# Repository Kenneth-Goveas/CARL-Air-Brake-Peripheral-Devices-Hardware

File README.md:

# CARL Air Brake Peripheral Devices Hardware

This repository contains the electronic hardware design for the peripheral
devices module of the [CARL Air Brake][cab-repo] computer. The CARL Air Brake
computer automatically controls a rocket air brake in flight, so that the
vehicle attains an apogee at the desired altitude. Its peripheral devices module
contains the necessary sensors and the brake actuator.

![Top view of the peripheral devices module](
  ./documentation/images/top_view.png
)

![Bottom view of the peripheral devices module](
  ./documentation/images/bottom_view.png
)

Detailed documentation for this repository can be found in the following files.

- [description.md][des]:
  Detailed description of the peripheral devices module.
- [cloning.md][cln]:
  Properly cloning this repository along with all its submodules.
- [prerequisites.md][req]:
  Necessary software for viewing and editing the electronic design.
- [organization.md][org]:
  Directory structure and organization of files in this repository.
- [flashing.md][fsh]:
  Flashing software onto the peripheral devices module.

[des]:      ./documentation/description.md
[cln]:      ./documentation/cloning.md
[req]:      ./documentation/prerequisites.md
[org]:      ./documentation/organization.md
[fsh]:      ./documentation/flashing.md

[cab-repo]: https://github.com/Kenneth-Goveas/CARL-Air-Brake

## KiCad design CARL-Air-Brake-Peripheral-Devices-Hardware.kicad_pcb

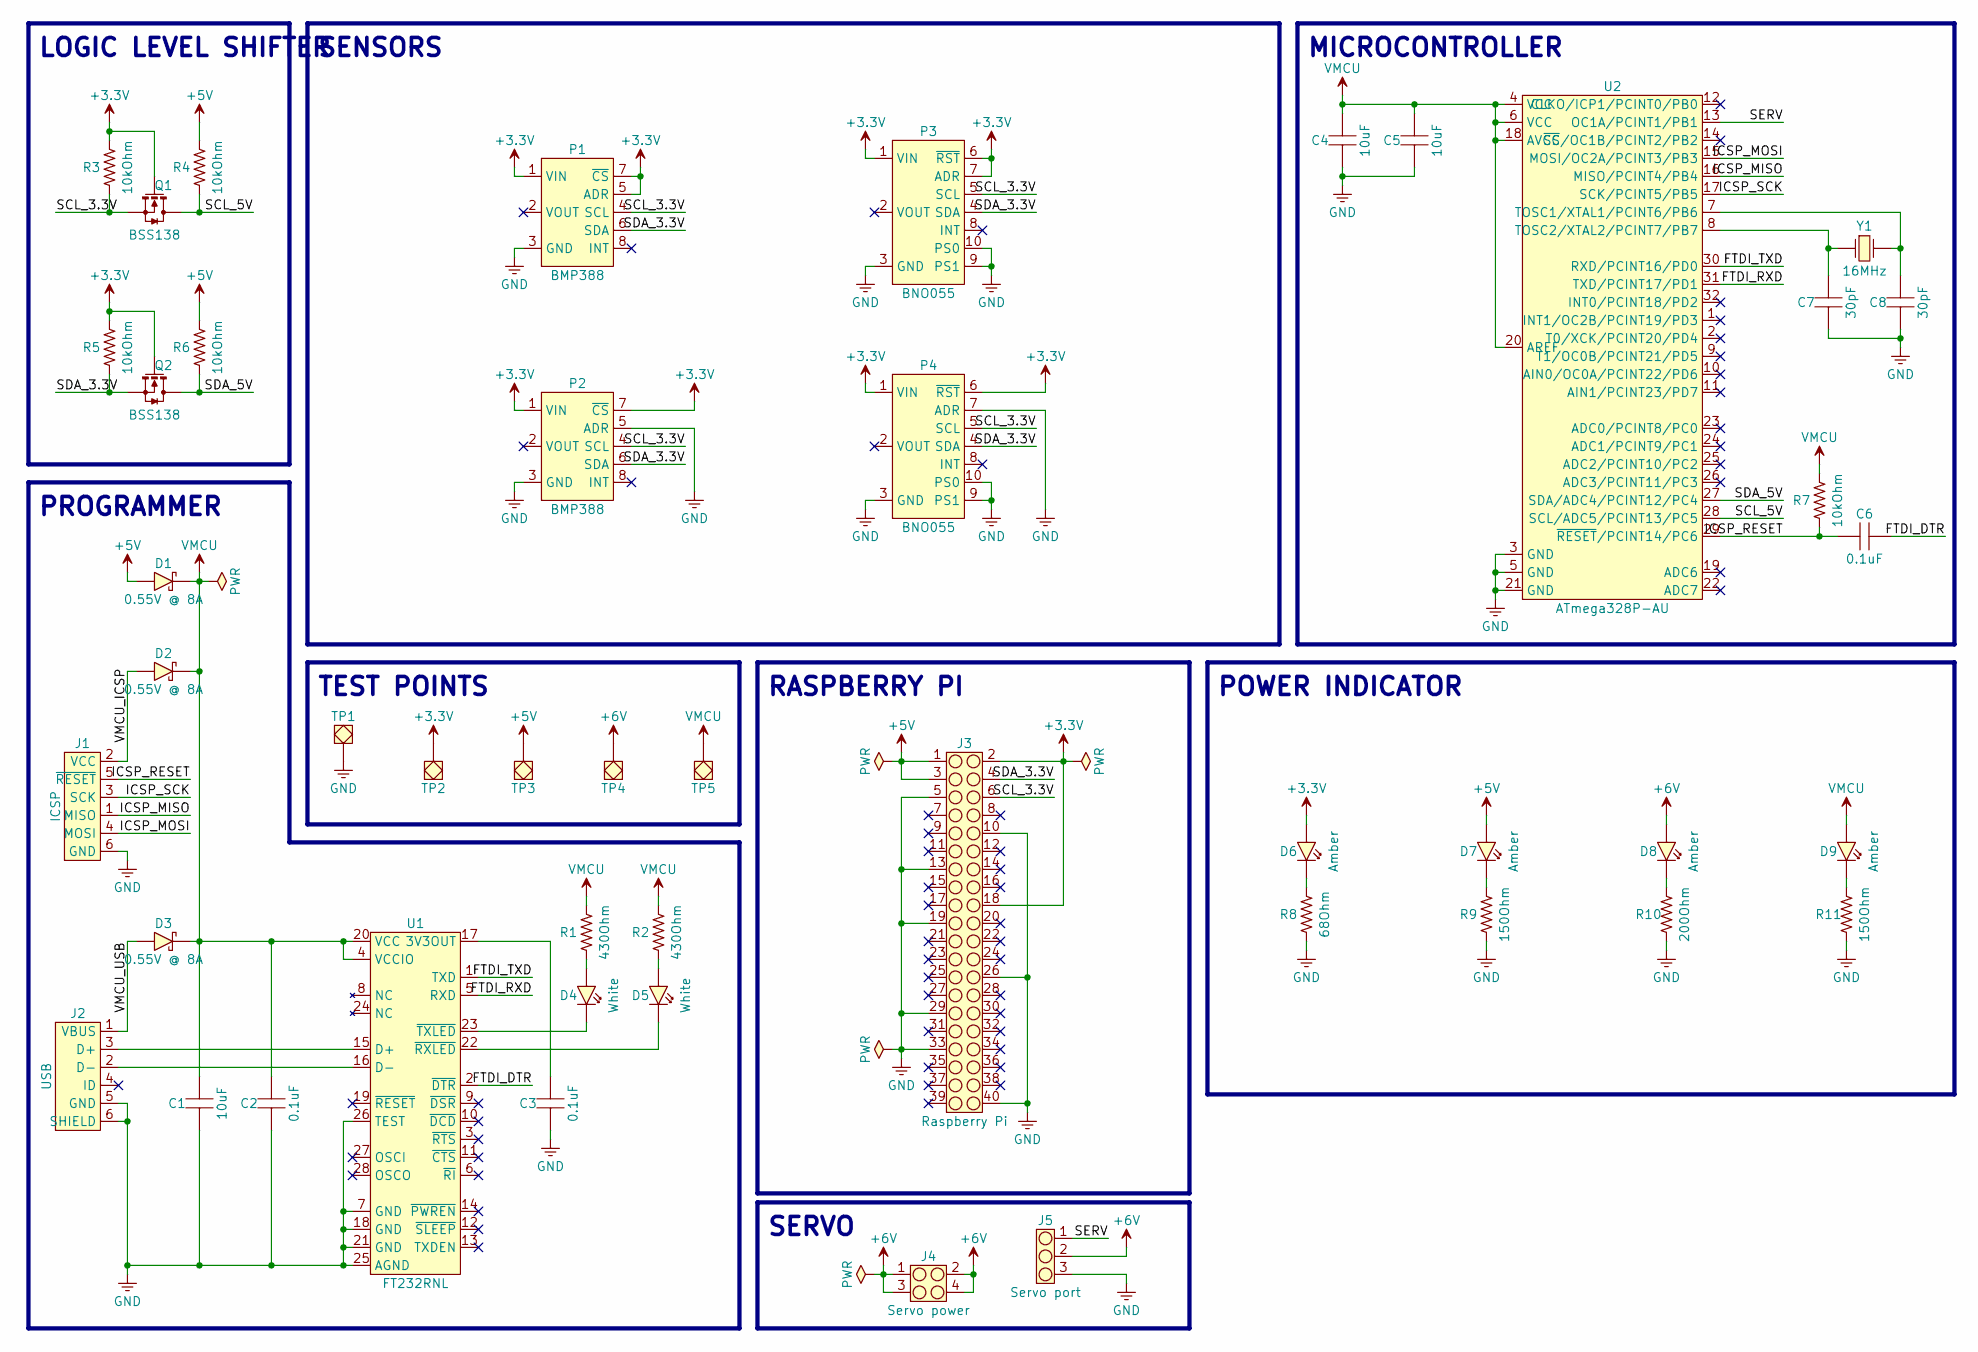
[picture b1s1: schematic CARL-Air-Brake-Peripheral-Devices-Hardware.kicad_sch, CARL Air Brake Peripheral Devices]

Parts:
C1, C4, C5: 10uF; Cap_Ceramic_0603
C2, C3, C6: 0.1uF; Cap_Ceramic_0603
C7, C8: 30pF; Cap_Ceramic_0603
D1, D2, D3: 0.55V @ 8A; Diode_DO-214AB_SMC
D4, D5: White; LED_0603
D6, D7, D8, D9: Amber; LED_0603
J1: ICSP; PinHead_02x03_Pitch2.54mm_Bot3.00mm_Top6.00mm_Shroud2.50mm
J2: USB; USB_Micro_B_Recp_Wuerth_629105136821
J3: Raspberry Pi; SockHead_02x20_Pitch2.54mm_Bot3.10mm_Top8.50mm
J4: Servo power; SockHead_02x02_Pitch2.54mm_Bot3.10mm_Top8.50mm
J5: Servo port; PinHead_01x03_Pitch2.54mm_Bot3.00mm_Top6.00mm_Shroud2.50mm
P1, P2: BMP388; Adafruit_BMP388
P3, P4: BNO055; Adafruit_BNO055
Q1, Q2: BSS138; SOT-23-3
R1, R2: 430Ohm; Res_Film_0603
R3, R4, R5, R6, R7: 10kOhm; Res_Film_0603
R8: 68Ohm; Res_Film_0603
R9, R11: 150Ohm; Res_Film_0603
R10: 200Ohm; Res_Film_0603
TP1, TP2, TP3, TP4, TP5: TestPoint_CircPad2.00mm_CircMsk2.50mm
U1: FT232RNL; SOIC_28_Dim5.50x10.50x2.00mm_Pitch0.65mm
U2: ATmega328P-AU; TQFP_08x08_Dim7.00x7.00x1.20mm_Pitch0.80mm
Y1: 16MHz; Crystal_HC49-US

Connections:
/FTDI_DTR: C6.2, U1.2 (~DTR)
/FTDI_RXD: U1.5 (RXD), U2.31 (TXD/PCINT17/PD1)
/FTDI_TXD: U1.1 (TXD), U2.30 (RXD/PCINT16/PD0)
/ICSP_MISO: J1.1 (MISO), U2.16 (MISO/PCINT4/PB4)
/ICSP_MOSI: J1.4 (MOSI), U2.15 (MOSI/OC2A/PCINT3/PB3)
/ICSP_RESET: C6.1, J1.5 (~RESET), R7.1, U2.29 (~RESET/PCINT14/PC6)
/ICSP_SCK: J1.3 (SCK), U2.17 (SCK/PCINT5/PB5)
/SCL_3.3V: J3.6, P1.4 (SCL), P2.4 (SCL), P3.5 (SCL), P4.5 (SCL), Q1.2 (S), R3.1
/SCL_5V: Q1.3 (D), R4.1, U2.28 (SCL/ADC5/PCINT13/PC5)
/SDA_3.3V: J3.4, P1.6 (SDA), P2.6 (SDA), P3.4 (SDA), P4.4 (SDA), Q2.2 (S), R5.1
/SDA_5V: Q2.3 (D), R6.1, U2.27 (SDA/ADC4/PCINT12/PC4)
/SERV: J5.1, U2.13 (OC1A/PCINT1/PB1)
/VMCU_ICSP: D2.1 (A), J1.2 (VCC)
/VMCU_USB: D3.1 (A), J2.1 (VBUS)
unnamed: D4.1 (A), R1.1
unnamed: D4.2 (K), U1.23 (~TXLED)
unnamed: D5.1 (A), R2.1
unnamed: D5.2 (K), U1.22 (~RXLED)
unnamed: D6.2 (K), R8.2
unnamed: D7.2 (K), R9.2
unnamed: D8.2 (K), R10.2
unnamed: D9.2 (K), R11.2
unnamed: J2.3 (D+), U1.15 (D+)
unnamed: J2.2 (D-), U1.16 (D-)
unnamed: C3.2, U1.17 (3V3OUT)
unnamed: C8.2, U2.7 (TOSC1/XTAL1/PCINT6/PB6), Y1.2
unnamed: C7.2, U2.8 (TOSC2/XTAL2/PCINT7/PB7), Y1.1

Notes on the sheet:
MICROCONTROLLER
RASPBERRY PI
LOGIC LEVEL SHIFTER
SENSORS
POWER INDICATOR
TEST POINTS
SERVO
PROGRAMMER

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
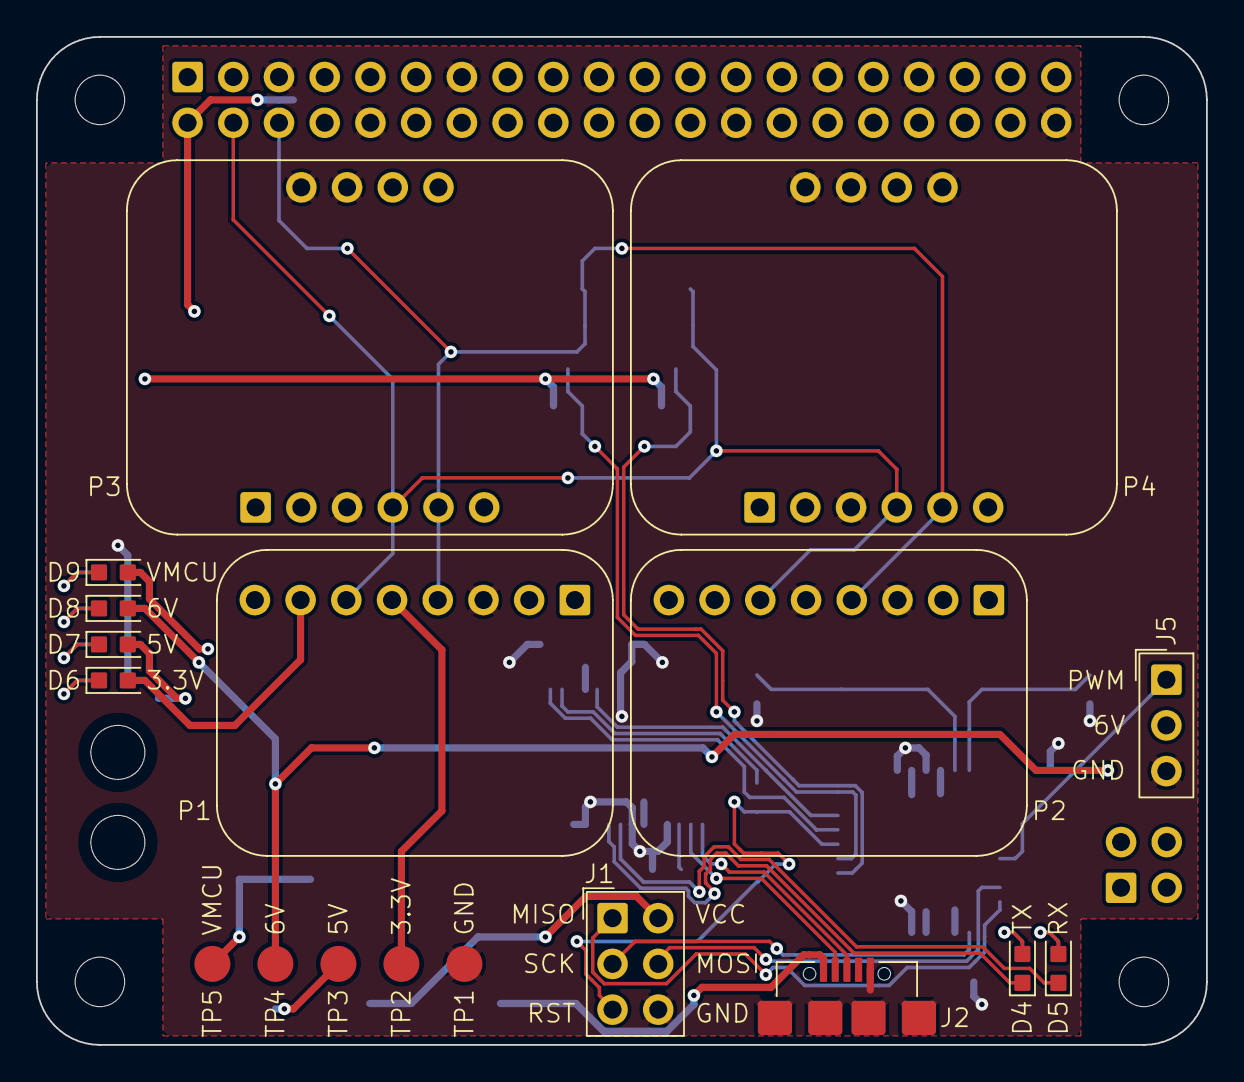
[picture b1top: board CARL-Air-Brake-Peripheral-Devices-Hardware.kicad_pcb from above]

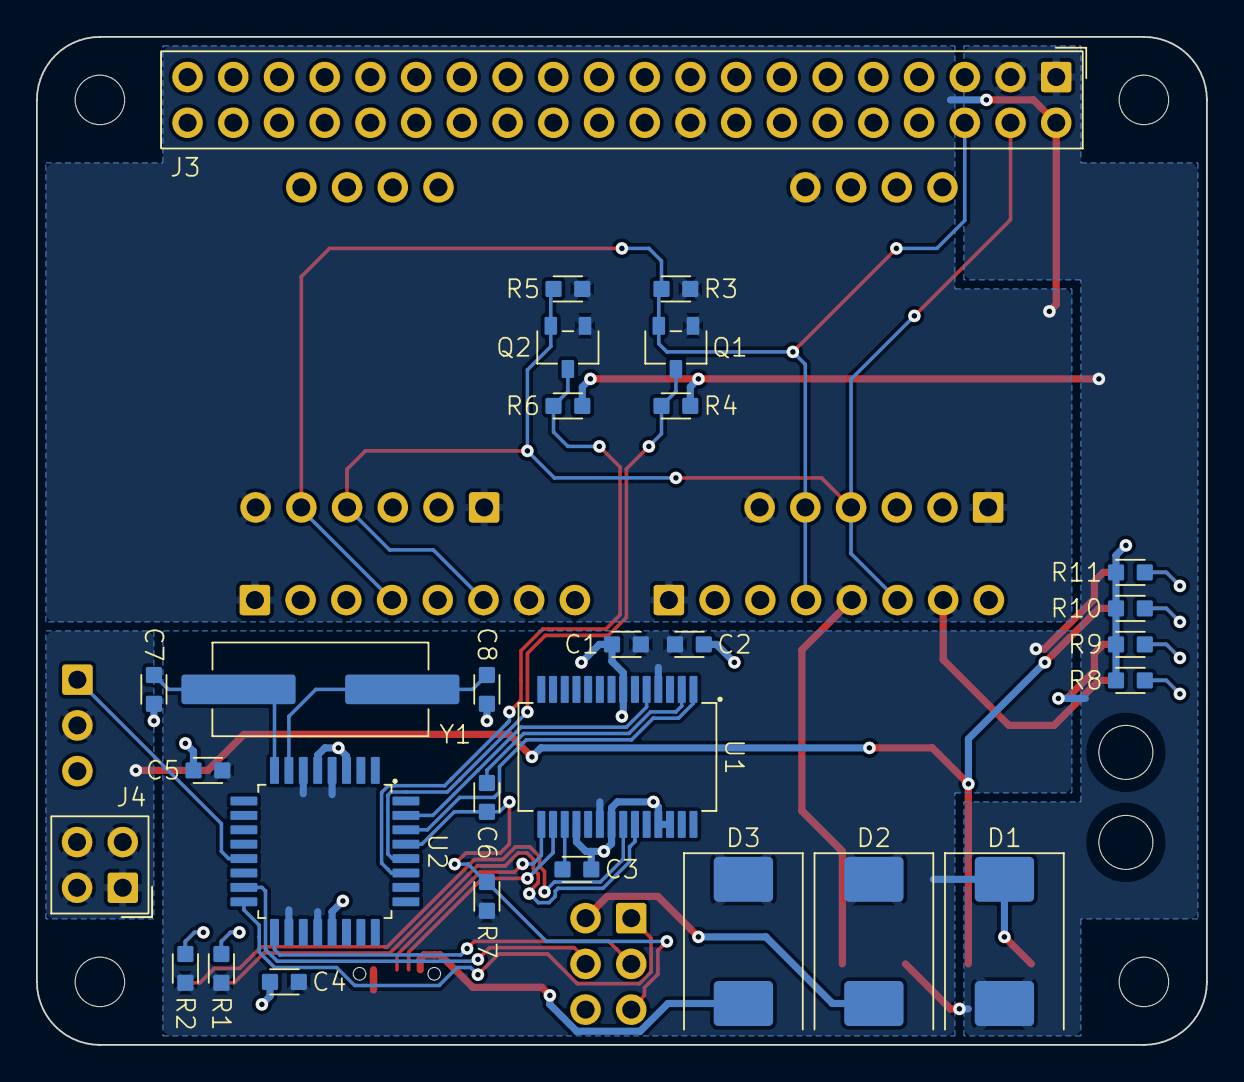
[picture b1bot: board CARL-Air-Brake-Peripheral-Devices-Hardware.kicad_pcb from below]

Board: 2 copper layers, 65.0 x 56.0 mm, 47 parts (29 on the bottom side), 32 nets.

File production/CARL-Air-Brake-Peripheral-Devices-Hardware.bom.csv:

Serial,Reference,Manufacturer,Part,Description,Quantity
1,R8,Yageo,AC0603FR-0768RL,Resistor 68Ohm 100mW 1% 0603,1
2,R9 R11,Yageo,RC0603FR-10150RL,Resistor 150Ohm 100mW 1% 0603,2
3,R10,Yageo,RC0603FR-07200RL,Resistor 200Ohm 100mW 1% 0603,1
4,R1 R2,Yageo,RT0603DRE07430RL,Resistor 430Ohm 100mW 0.5% 0603,2
5,R3 R4 R5 R6 R7,Yageo,RT0603FRE1310KL,Resistor 10kOhm 100mW 1% 0603,5
6,C7 C8,Murata,GRM1885C1H300GA01D,Capacitor 30pF 50V 2% 0603,2
7,C2 C3 C6,Murata,GCM188R71C104JA37D,Capacitor 0.1uF 16V 5% 0603,3
8,C1 C4 C5,Murata,GRT188R61C106KE13J,Capacitor 10uF 16V 10% 0603,3
9,D1 D2 D3,Diotec,SK84-AQ,Diode Schottky 0.55V @ 8A DO-214AB/SMC,3
10,D4 D5,Ams Osram,LW Q38G-Q1OO-3K6L-1,LED White 2.85V @ 5mA 0603,2
11,D6 D7 D8 D9,Wuerth,150060AS75000,LED Amber 2V @ 20mA 0603,4
12,Q1 Q2,Onsemi,BSS138,Logic Level Shift Transistor,2
13,Y1,ECS,ECS-160-20-5PX-TR,Crystal 16Mhz 20pF HC49-US,1
14,J1,Adam Tech,PH2-06-UA,Pin Header 2x3,1
15,J2,Wuerth,629105136821,Micro USB Receptacle,1
16,J3,Assmann WSW,A-BL254-DG-Z40D,Socket Header 2x20,1
17,J4,Assmann WSW,A-BL254-DG-Z04D,Socket Header 2x2,1
18,J5,Wuerth,61300311121,Pin Header 1x3,1
19,U1,FTDI,FT232RNL-REEL,USB-UART Bridge,1
20,U2,Microchip,ATmega328P-AU,8-Bit AVR Microcontroller,1
21,P1 P2,Adafruit,3966,BMP388 Module,2
22,P3 P4,Adafruit,4646,BNO055 Module,2

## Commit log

2024-06-24 Initialized repository
    Created empty repository with README.md file.
2025-07-19 Initialized repository
    Created empty repository with .gitignore file.
2025-07-19 Added KiCad library
    Cloned KiCad component library as submodule.
2025-07-19 Initialized KiCad project
    Created KiCad project files without any circuit design.
2025-07-20 Added schematic
    Completed circuit schematic and performed ERC.
2025-07-20 Assigned footprints
    Assigned footprints to all components in circuit schematic.
2025-07-20 Updated library
    Pulled latest updates to component library.
2025-07-20 Arranged components
    Created board layout and placed components at suitable locations.
2025-07-26 Added filled zones
    Added filled copper zones for high current power supply lines.
2025-07-30 Routed circuit board
    Completed circuit design by routing all connections, and performed DRC.
2026-01-06 Plotted gerber and drill files
    Configured settings for gerber and drill file generation and plotted
    gerber and drill files.
2026-01-06 Added bill of materials
    Added bill of materials to production directory.
2026-01-10 Added README
    Added README and supporting documentation.
